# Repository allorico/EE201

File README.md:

This branch is dedicated to my lab4 stuff. All of my deliverables for this part of the course can be found in the lab4 folder here.

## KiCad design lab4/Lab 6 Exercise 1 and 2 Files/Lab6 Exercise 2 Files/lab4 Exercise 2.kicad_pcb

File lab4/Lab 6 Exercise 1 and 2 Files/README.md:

This folder contains the files used for Lab6 that were originally from Lab4.

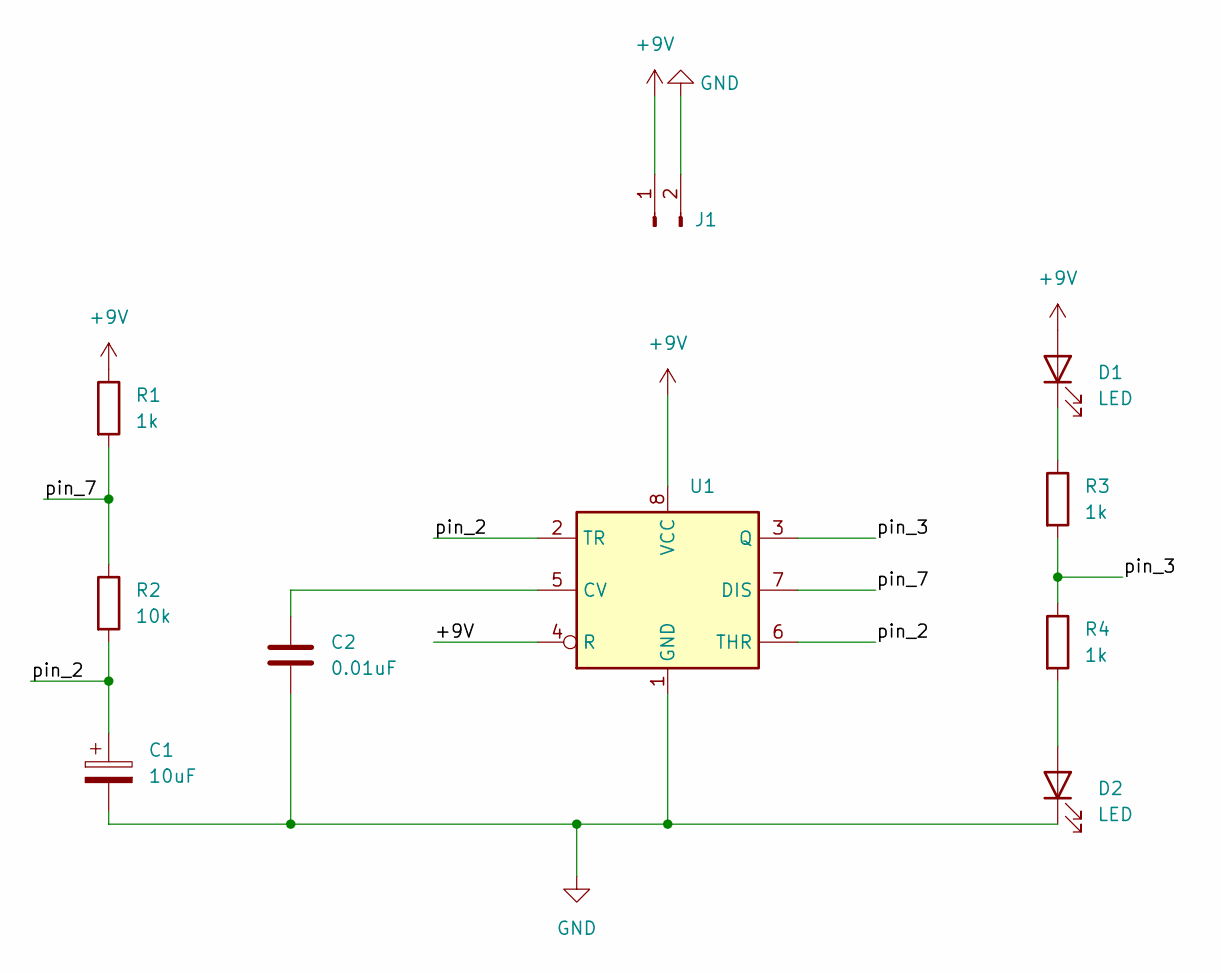
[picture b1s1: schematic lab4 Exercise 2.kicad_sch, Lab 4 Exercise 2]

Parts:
C1: 10uF; CP_EIA-3216-18_Kemet-A_Pad1.58x1.35mm_HandSolder
C2: 0.01uF; C_0805_2012Metric_Pad1.18x1.45mm_HandSolder
D1, D2: LED; LED_1206_3216Metric_Pad1.42x1.75mm_HandSolder
J1: Conn_01x02_Male; TerminalBlock_bornier-2_P5.08mm
R1, R3, R4: 1k; R_0805_2012Metric_Pad1.20x1.40mm_HandSolder
R2: 10k; R_0805_2012Metric_Pad1.20x1.40mm_HandSolder
U1: NE555D; SOIC-8-1EP_3.9x4.9mm_P1.27mm_EP2.29x3mm

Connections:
+9V: D1.2 (A), J1.1, R1.1, U1.4 (R), U1.8 (VCC)
/pin_2: C1.1, R2.2, U1.2 (TR), U1.6 (THR)
/pin_3: R3.2, R4.1, U1.3 (Q)
/pin_7: R1.2, R2.1, U1.7 (DIS)
GND: C1.2, C2.2, D2.1 (K), J1.2, U1.1 (GND)
unnamed: C2.1, U1.5 (CV)
unnamed: D1.1 (K), R3.1
unnamed: D2.2 (A), R4.2

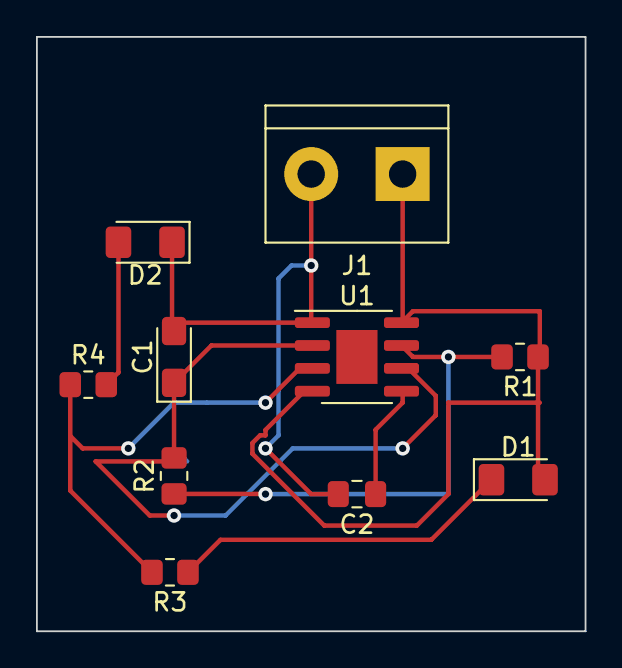
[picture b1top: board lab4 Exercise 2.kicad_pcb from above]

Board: 2 copper layers, 30.5 x 33.0 mm, 10 parts (0 on the bottom side), 8 nets.

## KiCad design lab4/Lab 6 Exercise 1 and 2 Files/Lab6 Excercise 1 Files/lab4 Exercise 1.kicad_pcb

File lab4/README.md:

This branch includes both the lab4 deliverables and another folder dedicated to lab6 stuff, which is stuff that was updated from lab4.

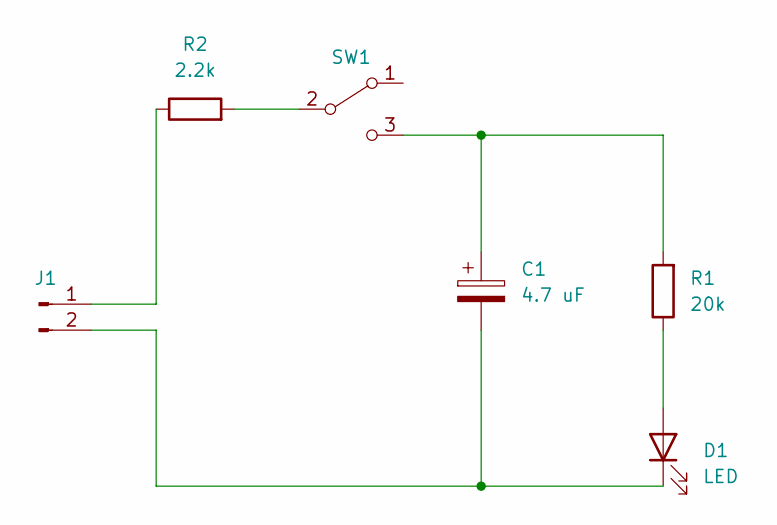
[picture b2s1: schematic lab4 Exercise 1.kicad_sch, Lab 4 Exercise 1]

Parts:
C1: 4.7 uF; C_Radial_D5.0mm_H5.0mm_P2.00mm
D1: LED; LED_D5.0mm
J1: Conn_01x02_Male; JST_PH_B2B-PH-K_1x02_P2.00mm_Vertical
R1: 20k; R_Axial_DIN0516_L15.5mm_D5.0mm_P20.32mm_Horizontal
R2: 2.2k; R_Axial_DIN0516_L15.5mm_D5.0mm_P20.32mm_Horizontal
SW1: SW_SPDT; SW_E-Switch_EG1224_SPDT_Angled

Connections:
unnamed: C1.1, R1.2, SW1.3 (C)
unnamed: C1.2, D1.1 (K), J1.2
unnamed: D1.2 (A), R1.1
unnamed: J1.1, R2.1
unnamed: R2.2, SW1.2 (B)

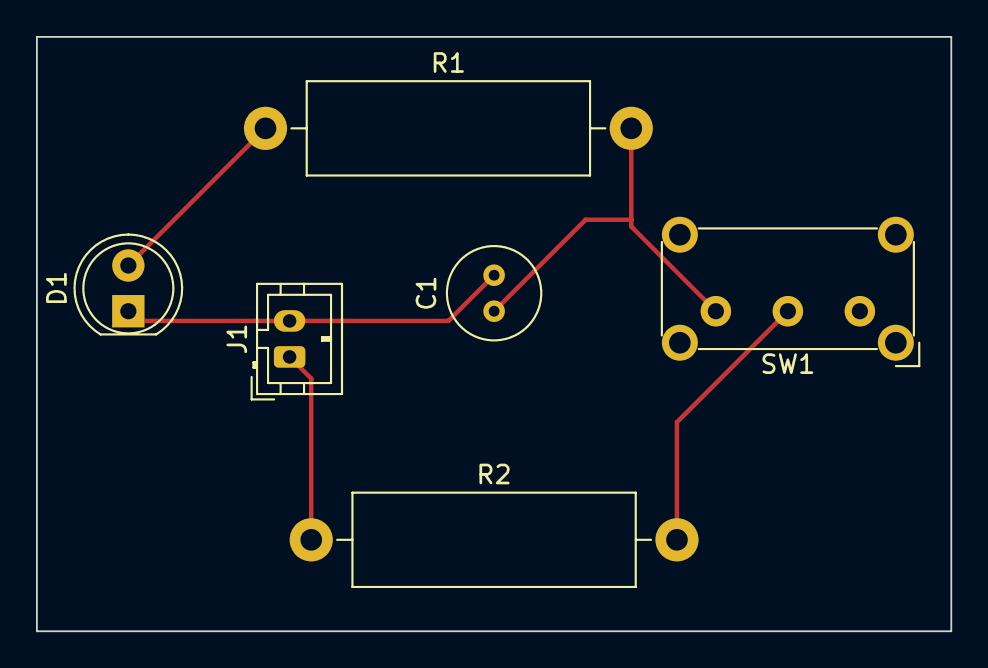
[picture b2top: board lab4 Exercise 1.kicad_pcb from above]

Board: 2 copper layers, 50.8 x 33.0 mm, 6 parts (0 on the bottom side), 5 nets.

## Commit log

2023-01-13 I made an edit to README
2023-01-13 added directory aboutMe and added README in that new directory
2023-01-13 edit to README
2023-01-13 edited README
2023-01-14 created aboutMe in aboutMe branch
2023-01-14 Completed aboutMe README file
2023-01-14 edited READ ME
2023-01-20 Created Arduino branch, file, and README
2023-01-20 edited README folder specifically for this arduino branch
2023-01-20 Added code used for exercises 2, 3 and 4
2023-01-27 created lab4 branch and folder
2023-01-27 added lab exercise pdfs
2023-02-03 added soldering pics
2023-02-16 Added Lab6 stuff
2023-02-24 added lab 7 files
2023-03-15 added lab8 images
